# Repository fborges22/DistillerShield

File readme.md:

# Distiller Shield LATE

The distiller shield is an arduino based module to control the distiller developed in the LATE Laboratory from the department of chemistry of the State's University of Londrina (UEL).

## Usage

Use the KiCAD to open the schematic and the PCB files. You also need to generate the gerber files to send to manufacturing.

## Contributing
Pull requests are welcome. For major changes, please open an issue first to discuss what you would like to change.

Please make sure to update tests as appropriate.

## Credits
Felipe Andrade Allemand Borges\
Gabriel Gardin\
Mario Henrique Killner

## License
[MIT](https://choosealicense.com/licenses/mit/)

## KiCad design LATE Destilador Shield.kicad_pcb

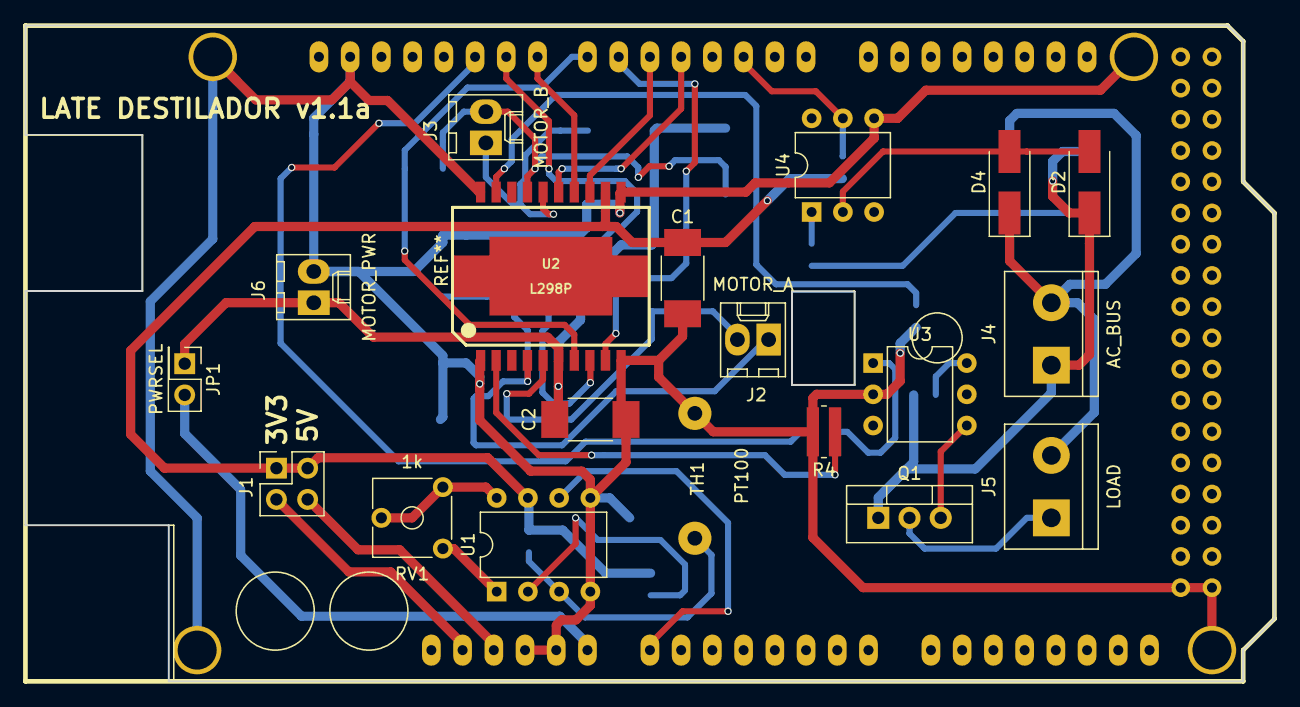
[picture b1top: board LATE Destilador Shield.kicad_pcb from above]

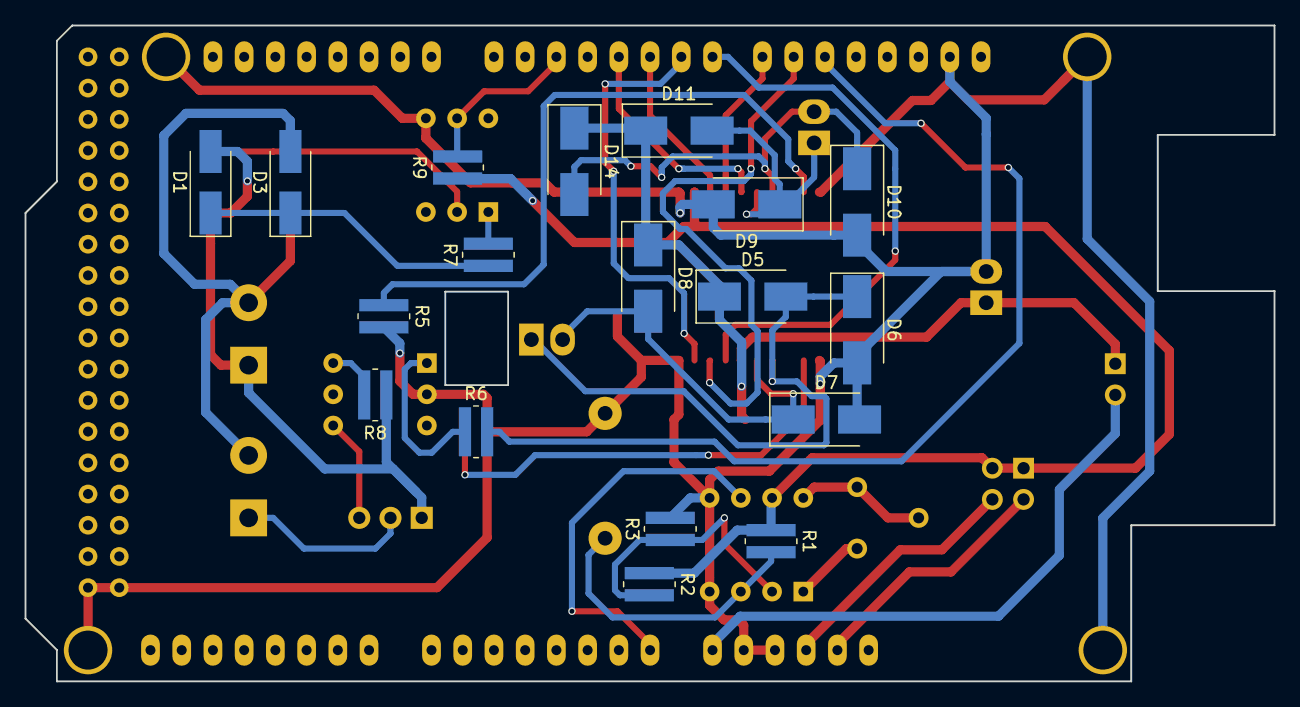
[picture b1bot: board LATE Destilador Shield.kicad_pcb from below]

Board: 2 copper layers, 101.6 x 53.3 mm, 38 parts (18 on the bottom side), 34 nets.

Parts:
C1: 470u; C_1812_HandSoldering
C2: 100nF; C_1812_HandSoldering
D1, D2, D3, D4: 1N4004; D_SMA_Handsoldering
D5, D6, D7, D8, D9, D10, D11, D14: SS26; D_SMB_Handsoldering
J1: PWRSRC; Pin_Header_Straight_2x02_Pitch2.54mm
J2: MOTOR_A; Molex_KK-6410-02_02x2.54mm_Straight
J3: MOTOR_B; Molex_KK-6410-02_02x2.54mm_Straight
J4: AC_BUS; TerminalBlock_bornier-2_P5.08mm
J5: LOAD; TerminalBlock_bornier-2_P5.08mm
J6: MOTOR_PWR; Molex_KK-6410-02_02x2.54mm_Straight
JP1: PWRSEL; Pin_Header_Straight_2x01_Pitch2.54mm
LATE DESTILADOR v1.1a: ARDUINO_MEGA_SHIELD
Q1: BT136-500; TO-220-3_Vertical
R1, R2, R3: 100; R_1508_Wide
R4, R5: 10; R_1508_Wide
R6: 220; R_1508_Wide
R7, R8: 330; R_1508_Wide
R9: 1k; R_1508_Wide
RV1: 1k; Potentiometer_Trimmer_ACP_CA6v_Horizontal
TH1: PT100; WireConnection_1.20mmDrill
U1: AD620; DIP-8_W7.62mm
U2: L298P; PowerSO-20
U3: MOC3020M; DIP-6_W7.62mm
U4: 4N25; DIP-6_W7.62mm

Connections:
3V3: J1.3, LATE DESTILADOR v1.1a.3V3
5VDC: J1.4, LATE DESTILADOR v1.1a.5V
+12V: C2.1, D5.1, D8.1, D11.1, D14.1, J6.1, JP1.1, U2.6
/ENA: LATE DESTILADOR v1.1a.9, U2.8
/ENB: LATE DESTILADOR v1.1a.8, U2.14
/IN1: LATE DESTILADOR v1.1a.7, U2.7
/IN2: LATE DESTILADOR v1.1a.6, U2.9
/IN3: LATE DESTILADOR v1.1a.5, U2.13
/IN4: LATE DESTILADOR v1.1a.4, U2.15
AC1: D1.2, D2.1, J4.1, Q1.1, R8.1
AC2: D3.2, D4.1, J4.2, J5.2
ACINT: LATE DESTILADOR v1.1a.2, R9.2, U4.5
GND: C1.2, C2.2, D6.2, D7.2, D9.2, D10.2, J6.2, LATE DESTILADOR v1.1a.GND1, LATE DESTILADOR v1.1a.GND2, LATE DESTILADOR v1.1a.GND3, LATE DESTILADOR v1.1a.GND4, LATE DESTILADOR v1.1a.GND5, R3.2, R4.2, R5.2, TH1.2, U1.4, U1.5, U2.1, U2.10, U2.11, U2.20, U3.2, U4.4
unnamed: D1.1, D3.1, R7.1
unnamed: D2.2, D4.2, U4.2
unnamed: D5.2, D6.1, J2.1, U2.4
unnamed: D7.1, D8.2, J2.2, U2.5
unnamed: D10.1, D14.2, J3.2, U2.17
unnamed: D9.1, D11.2, J3.1, U2.16
unnamed: J5.1, Q1.2
unnamed: JP1.2, LATE DESTILADOR v1.1a.V_IN
unnamed: Q1.3, U3.4
unnamed: R1.2, TH1.1, U1.3
unnamed: R2.2, R3.1, U1.2
unnamed: R4.1, U2.2
unnamed: R5.1, U2.19
unnamed: R6.1, U3.1
unnamed: R7.2, U4.1
unnamed: R8.2, U3.6
unnamed: RV1.1, RV1.2, U1.8
unnamed: RV1.3, U1.1
unnamed: LATE DESTILADOR v1.1a.AD0, U1.6
TRIG: LATE DESTILADOR v1.1a.10, R6.2
VCC: C1.1, J1.1, J1.2, R1.1, R2.1, R9.1, U1.7, U2.12

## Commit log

2019-02-04 First commit after migration from SVN
2019-02-21 Project upgrade to KiCAD 5.02
